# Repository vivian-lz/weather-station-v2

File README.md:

# weather-station-v2
To expand on my first weather station product, I am creating a more advanced version that uses PCB design, I2C communication, and STM32/ESP32 microcontrollers.

The first iteration utilizes the ESP32 module as the base microcontroller and a BME280 module as the main chip that senses the temperature, humidity, pressue, and approximate altitude. This PCB has been created but has not yet been assembled or manufactured.

Since circuits that utilize modules often are constrained by size and control over communication, I also wanted to dive deeper into circuit design by creating a device that utilizes the raw IC chips rather than just modules. I am currently in the process of creating the schematic for this device, which utilizes an ESP32 C6FH4 and the raw BME280 IC. In addition, it utilizes USB-C connection with a USB-to-Serial chip for communication as well as a MIC5365 LDO to drop the voltage that enters the USB from 5 to 3.3 V before it enters the ESP32 chip to avoid frying the chip/board. This device also includes a 40 kHz crystal to generate a constant clock signal for the device and a reset button to manually reset the ESP32 if needed. Finally, the device still contains the traditional RGB and the LCD of the original design to display information in different ways.

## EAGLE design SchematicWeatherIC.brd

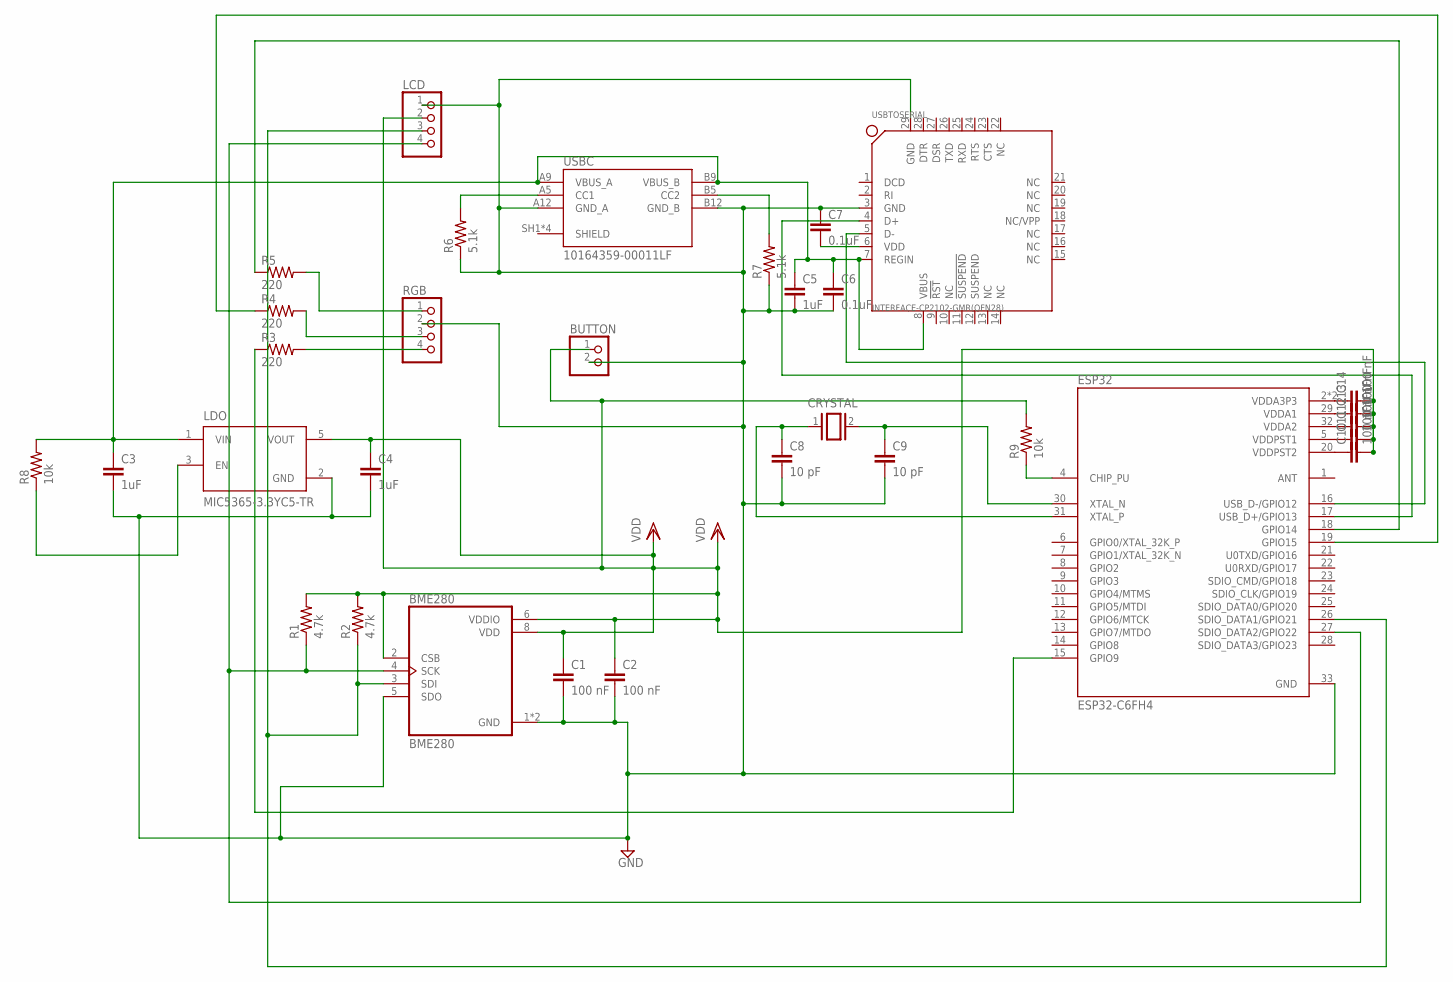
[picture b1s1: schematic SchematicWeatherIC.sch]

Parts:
BME280: BME280; PSON65P250X250X100-8N
BUTTON: PINHD-1X2; 1X02
C1, C2, C10, C11, C12, C13, C14: 100 nF; C5B3
C3, C4, C5: 1uF; C5B2.5
C6, C7: 0.1uF; C5B2.5
C8, C9: 10 pF; C5B3
CRYSTAL: XTAL/S; QS
ESP32: ESP32-C6FH4; QFN50P500X500X90-33N
LCD: PINHD-1X4; 1X04
LDO: MIC5365-3.3YC5-TR; SOT65P210X110-5N
R1, R2: 4.7k; VMTA55
R3, R4, R5: 220; VMTA55
R6, R7: 5.1k; VMTA55
R8, R9: 10k; VMTA55
RGB: PINHD-1X4; 1X04
USBC: 10164359-00011LF; AMPHENOL_10164359-00011LF
USBTOSERIAL: INTERFACE-CP2102-GMR(QFN28); QFN28G_0.5-5X5MM

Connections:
D_N: ESP32.16 (USB_D-/GPIO12), USBTOSERIAL.5 (D-)
D_P: ESP32.17 (USB_D+/GPIO13), USBTOSERIAL.4 (D+)
GND: BME280.1 (GND), BME280.5 (SDO), BME280.7 (GND), BUTTON.2, C1.2, C2.2, C3.2, C4.2, C5.2, C6.2, C7.1, C8.2, C9.2, ESP32.33 (GND), LCD.1, LDO.2 (GND), R6.1, R7.1, RGB.2, USBC.A12 (GND_A), USBC.B12 (GND_B), USBTOSERIAL.3 (GND), USBTOSERIAL.29 (GND)
unnamed: ESP32.15 (GPIO9), R3.1
unnamed: C3.1, C5.1, C6.1, LDO.1 (VIN), R8.2, USBC.A9 (VBUS_A), USBC.B9 (VBUS_B), USBTOSERIAL.7 (REGIN), USBTOSERIAL.8 (VBUS)
unnamed: ESP32.4 (CHIP_PU), R9.1
unnamed: ESP32.18 (GPIO14), R5.1
unnamed: C7.2, USBTOSERIAL.6 (VDD)
unnamed: LDO.3 (EN), R8.1
unnamed: ESP32.19 (GPIO15), R4.1
unnamed: R3.2, RGB.4
unnamed: R4.2, RGB.3
unnamed: R5.2, RGB.1
unnamed: C8.1, CRYSTAL.1, ESP32.31 (XTAL_P)
unnamed: R6.2, USBC.A5 (CC1)
unnamed: R7.2, USBC.B5 (CC2)
unnamed: C10.1, ESP32.20 (VDDPST2)
unnamed: C9.1, CRYSTAL.2, ESP32.30 (XTAL_N)
unnamed: C11.1, ESP32.5 (VDDPST1)
unnamed: C12.1, ESP32.32 (VDDA2)
unnamed: C13.1, ESP32.29 (VDDA1)
unnamed: C14.1, ESP32.2 (VDDA3P3), ESP32.3 (VDDA3P3)
SCL: BME280.4 (SCK), ESP32.27 (SDIO_DATA2/GPIO22), LCD.4, R1.1
SDA: BME280.3 (SDI), ESP32.26 (SDIO_DATA1/GPIO21), LCD.3, R2.1
VDD: BME280.2 (CSB), BME280.6 (VDDIO), BME280.8 (VDD), BUTTON.1, C1.1, C2.1, C4.1, C10.2, C11.2, C12.2, C13.2, C14.2, LCD.2, LDO.5 (VOUT), R1.2, R2.2, R9.2

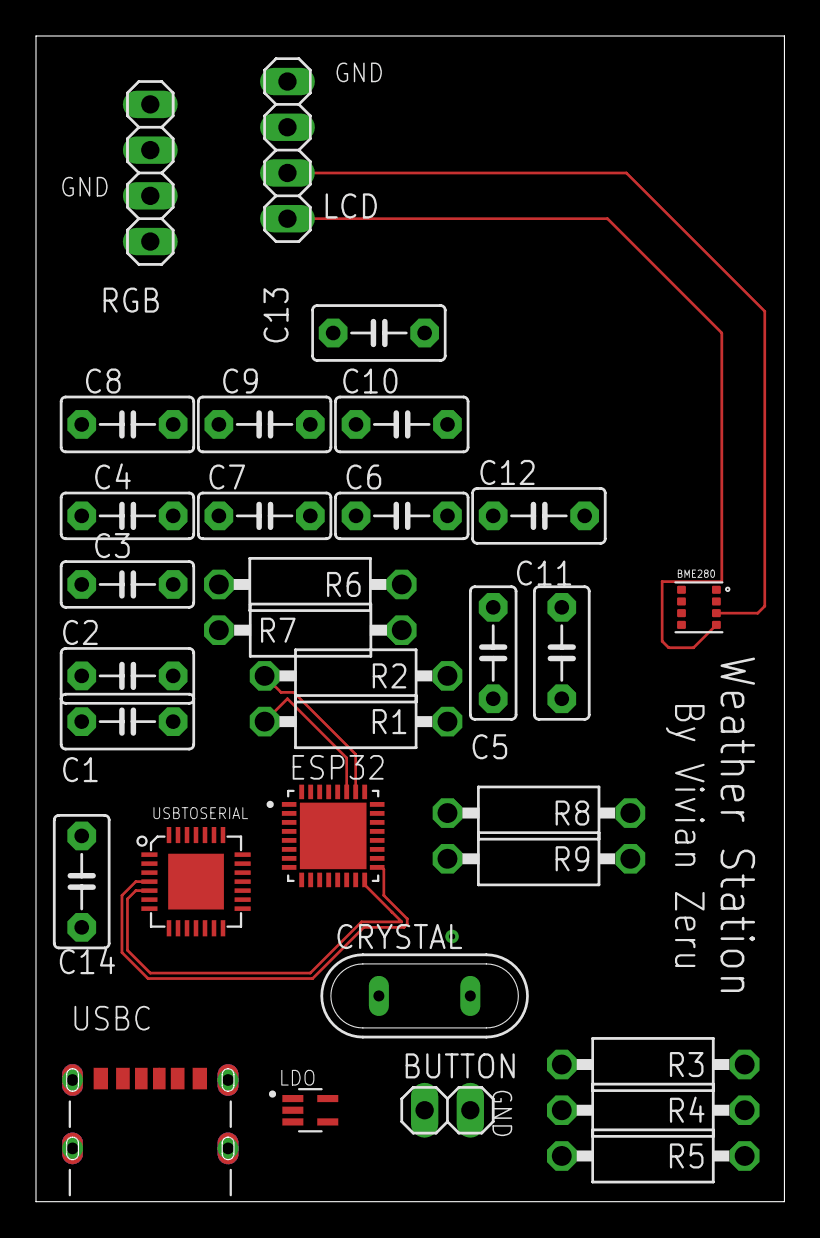
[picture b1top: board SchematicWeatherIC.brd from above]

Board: 2 copper layers, 41.6 x 64.8 mm, 32 parts (0 on the bottom side), 25 nets.

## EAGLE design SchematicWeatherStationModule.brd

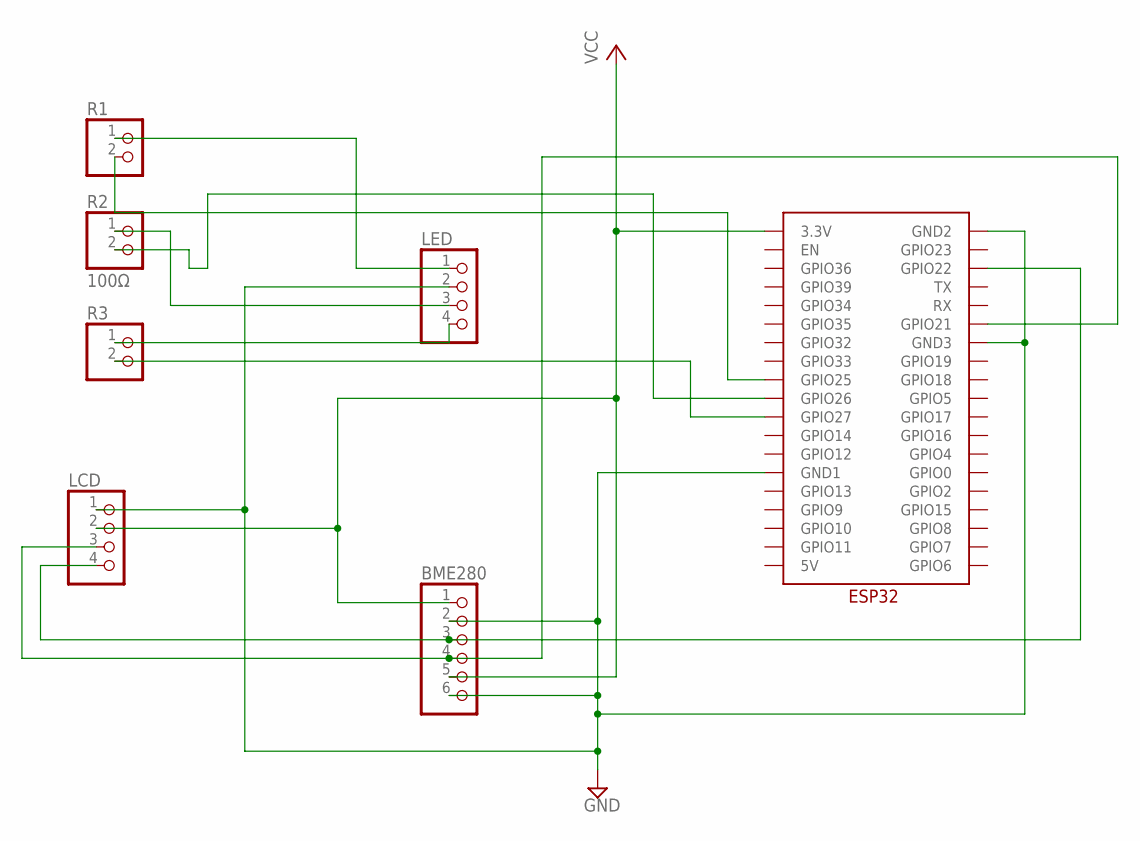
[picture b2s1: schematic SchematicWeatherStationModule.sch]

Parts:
BME280: PINHD-1X6/90; 1X06/90
LCD: PINHD-1X4/90; 1X04/90
LED: PINHD-1X4; 1X04
R1, R3: PINHD-1X2; 1X02
R2: 100Ω; 1X02
U$1: ESP32

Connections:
GND: BME280.2, BME280.6, LCD.1, LED.2, U$1.GND1, U$1.GND2, U$1.GND3
unnamed: LED.1, R1.1
unnamed: LED.3, R2.1
unnamed: LED.4, R3.1
unnamed: R3.2, U$1.GPIO27
unnamed: R1.2, U$1.GPIO25
unnamed: R2.2, U$1.GPIO26
SCL: BME280.3, LCD.4, U$1.GPIO22
SDA: BME280.4, LCD.3, U$1.GPIO21
VCC: BME280.1, BME280.5, LCD.2, U$1.3.3V

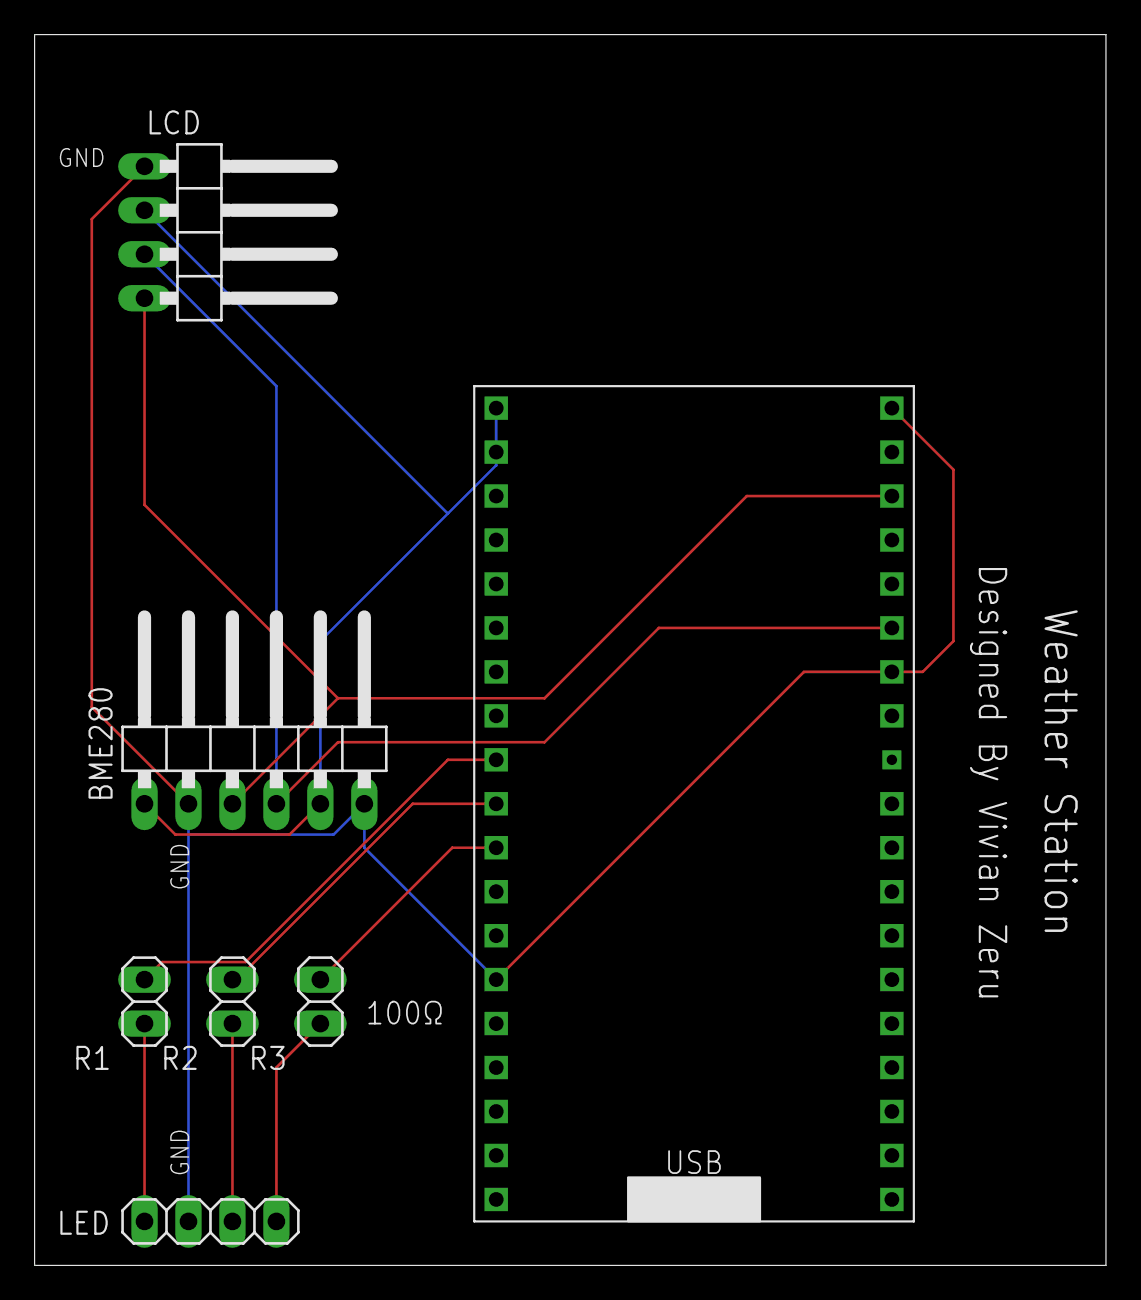
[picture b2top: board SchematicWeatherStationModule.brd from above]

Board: 2 copper layers, 61.9 x 71.1 mm, 7 parts (0 on the bottom side), 10 nets.

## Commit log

2025-06-25 Schematic and Layout (using Modules)
    This PCB schematic and layout was designed in Eagle and uses both the ESP32 and BME280 module in its design.
2025-07-22 adding all components and starting connections
2025-07-24 finish mostly all connections except to esp32 ic
2025-07-24 add crystal connection
2025-07-25 add lcd and some vdd connections
2025-07-25 all main connections on schematic complete
2025-07-25 connect vdd esp32
2025-07-25 some extra touches
2025-07-25 created board and moved in components to layout
2025-07-26 add decoupling capacitors to power
2025-07-26 add updates due to schematic update
2025-07-30 use smaller resistors and autoroute
2025-07-30 add smaller resistors and autoroute
2025-07-30 update name to label old board
2025-08-04 some wiring and routing updates in progress
2025-08-04 this is where the routing updates are in progress
2025-08-10 routed differential pair and i2c
